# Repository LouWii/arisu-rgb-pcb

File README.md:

# Arisu Keyboard PCB - RGB & DIY mod

Arisu RGB Keyboard PCB, originally designed by [FateNozomi](https://github.com/FateNozomi), modified by [LouWii](https://github.com/LouWii).

The main differences with the original design are:

* RGB LEDs added for underglow (12 LEDs)
* Some components replaced with their through-hole version for easy soldering
* Micro-USB replaced with a mini-USB with through-hole soldering (for better strength)

The layout remains **unchanged** from the original design.

Original presentation:

> アリス PCB designed using KiCad. The layout is inspired by Lyn's EM7 and TGR Alice with some modification of my own.
>
> Key differences:
>
> * I removed the extra [B] key on the right half and shifted the [NM,.?] row to the left by 0.25U.
> * Shifted the 3 keys to the right and added arrow keys.
> * Tweaked the bottom so that the 1.5U keys doesn't protrude out a little.

> Shifting the [NM,.?] row to the left by 0.25U required quite some work on the arrangement of keys for the right half.
> As a result, this does not give the same typing experience as Lyn's EM7 and TGR Alice.
> Lyn's EM7 and TGR Alice uses the home row as the center point to vertically align both halves while I used the number row instead.
> Due to the nature of staggered keyboards, aligning using the number row resulted in the home row not being aligned.

Disclaimer: Use these files at your own risk.

## Gerber Files
Download the gerber files under [releases](https://github.com/FateNozomi/arisu-pcb/releases).

## Assembly
For the components required, you may refer to the bill of materials included along with the release as reference or load up the design file in KiCad.
All the components can be soldered using a regular soldering iron, though soldering the Micro USB receptacle might be the biggest hurdle.

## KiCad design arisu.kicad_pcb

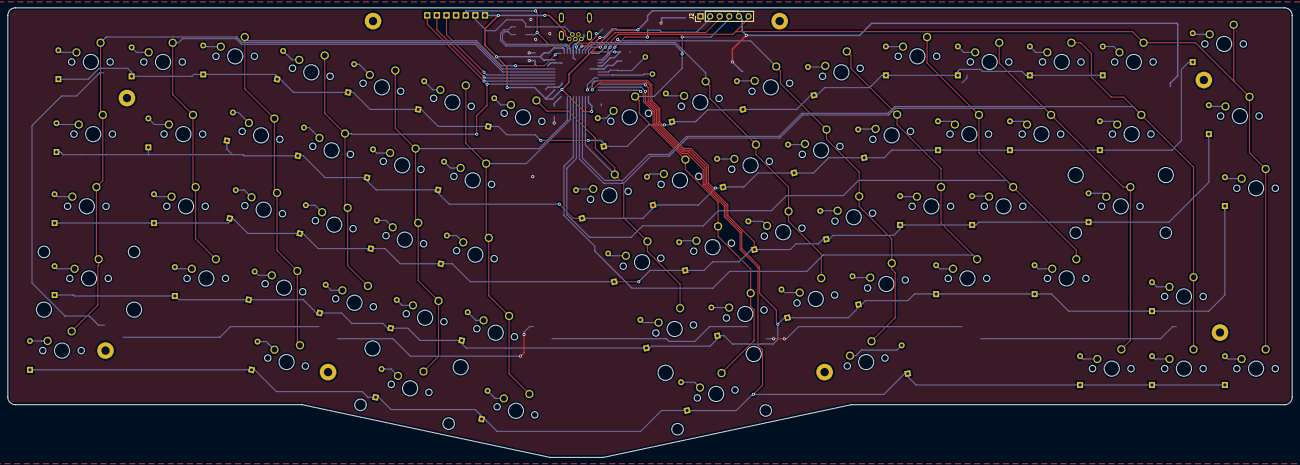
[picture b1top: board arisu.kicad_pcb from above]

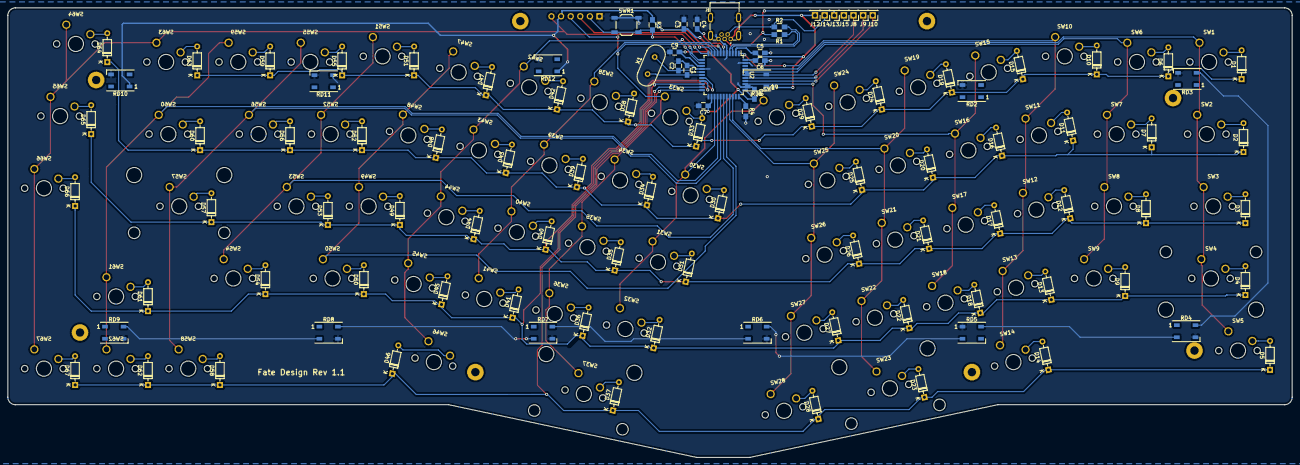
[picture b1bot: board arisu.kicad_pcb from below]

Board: 2 copper layers, 339.1 x 118.7 mm, 179 parts (103 on the bottom side), 114 nets.

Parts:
C1, C2: 22pF; C_0805_HandSoldering
C3: 10uF; C_0805_HandSoldering
C4: 1uF (±10%); C_0805_HandSoldering
C5: 1uF; C_0805_HandSoldering
C6, C7, C8, C9: 0.1uF; C_0805_HandSoldering
D1, D2, D3, D4, D5, D6, D7, D8, D9, D10, D11, D12, D13, D14, D15, D16, D17, D18, D19, D20, D21, D22, D23, D24, D25, D26, D27, D28, D29, D30, D31, D32, D33, D34, D35, D36, D37, D38, D39, D40, D41, D42, D43, D44, D45, D46, D47, D48, D49, D50, D51, D52, D53, D54, D55, D56, D57, D58, D59, D60, D61, D62, D63, D64, D65, D66, D67: D; D_DO-35_SOD27_P7.62mm_Horizontal
H1, H2, H3, H4, H5, H6, H7, H8: MountingHole; MountingHole_2.2mm_M2_Pad
J1: USB_B_Mini; Mini-USB-B_OMRON_XM7D-0512
J2: 1x6 2.54mm; PinHeader_1x06_P2.54mm_Vertical
J8: PF4; PinHeader_1x01_P2.54mm_Vertical
J9: PF5; PinHeader_1x01_P2.54mm_Vertical
J10: PF6; PinHeader_1x01_P2.54mm_Vertical
J12: VCC; PinHeader_1x01_P2.54mm_Vertical
J13: D+; PinHeader_1x01_P2.54mm_Vertical
J14: D-; PinHeader_1x01_P2.54mm_Vertical
J15: GND; PinHeader_1x01_P2.54mm_Vertical
R1, R2: 22; R_0805_HandSoldering
R3, R4: 10K; R_0805_HandSoldering
RD1, RD2, RD3, RD4, RD5, RD6, RD7, RD8, RD9, RD10, RD11, RD12: WS2812B; LED_WS2812B_PLCC4_5.0x5.0mm_P3.2mm
SW1, SW6, SW7, SW8, SW9, SW10, SW11, SW12, SW13, SW15, SW16, SW17, SW18, SW19, SW20, SW21, SW22, SW24, SW25, SW26, SW27, SW28, SW29, SW30, SW31, SW32, SW33, SW34, SW35, SW36, SW38, SW39, SW40, SW41, SW42, SW43, SW44, SW45, SW47, SW48, SW49, SW50, SW51, SW52, SW53, SW55, SW56, SW58, SW59, SW61, SW62, SW63, SW64, SW65, SW66, SW67: SW_Push; SW_Cherry_MX_1.00u_PCB
SW2, SW5, SW14, SW46, SW60: SW_Push; SW_Cherry_MX_1.50u_PCB
SW3, SW54: SW_Push; SW_Cherry_MX_1.75u_PCB
SW4: SW_Push; SW_Cherry_MX_2.25u_PCB
SW23: SW_Push; SW_Cherry_MX_2.00u_PCB_ReversedStabilizers
SW37: SW_Push; SW_Cherry_MX_2.75u_PCB_ReversedStabilizers
SW57: SW_Push; SW_Cherry_MX_2.25u_PCB_ReversedStabilizers
SWR1: SW_Push; SW_SPST_TL3342
U2: ATmega32U4-AU; TQFP-44_10x10mm_P0.8mm
X1: 16Mhz; Crystal_HC49-U_Vertical

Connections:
/MISO: J2.6, SW63.1, SW64.1, SW65.1, SW66.1, SW67.1, U2.11
/MOSI: J2.3, U2.10
/PF4: J8.1, U2.39
/PF5: J9.1, U2.38
/PF6: J10.1, U2.37
/SCK: J2.4, SW33.1, SW34.1, SW35.1, SW36.1, SW37.1, U2.9
/col0: SW1.1, SW2.1, SW3.1, SW4.1, SW5.1, U2.41
/col1: SW6.1, SW7.1, SW8.1, SW9.1, U2.40
/col2: SW10.1, SW11.1, SW12.1, SW13.1, SW14.1, U2.1
/col3: SW15.1, SW16.1, SW17.1, SW18.1, U2.36
/col4: SW19.1, SW20.1, SW21.1, SW22.1, SW23.1, U2.31
/col5: SW24.1, SW25.1, SW26.1, SW27.1, SW28.1, U2.30
/col6: SW29.1, SW30.1, SW31.1, SW32.1, U2.25
/col8: SW38.1, SW39.1, SW40.1, SW41.1, U2.8
/col9: SW42.1, SW43.1, SW44.1, SW45.1, SW46.1, U2.12
/col10: SW47.1, SW48.1, SW49.1, SW50.1, U2.29
/col11: SW51.1, SW52.1, SW53.1, SW54.1, U2.28
/col12: SW55.1, SW56.1, SW57.1, SW58.1, U2.27
/col13: SW59.1, SW60.1, SW61.1, SW62.1, U2.26
/row0: D1.1, D6.1, D10.1, D15.1, D19.1, D24.1, D29.1, D33.1, D38.1, D42.1, D47.1, D51.1, D55.1, D59.1, D63.1, U2.18
/row1: D2.1, D7.1, D11.1, D16.1, D20.1, D25.1, D30.1, D34.1, D39.1, D43.1, D48.1, D52.1, D56.1, D60.1, D64.1, U2.19
/row2: D3.1, D8.1, D12.1, D17.1, D21.1, D26.1, D31.1, D35.1, D40.1, D44.1, D49.1, D53.1, D57.1, D65.1, U2.20
/row3: D4.1, D9.1, D13.1, D18.1, D22.1, D27.1, D32.1, D36.1, D41.1, D45.1, D50.1, D54.1, D61.1, D66.1, U2.21
/row4: D5.1, D14.1, D23.1, D28.1, D37.1, D46.1, D58.1, D62.1, D67.1, U2.22
/~RES~: J2.2, R3.2, SWR1.2, U2.13
D+: R1.1, U2.4
D-: R2.1, U2.3
GND: C1.1, C2.2, C3.2, C4.2, C5.2, C6.2, C7.2, C8.2, C9.2, J1.5, J1.6, J2.1, J15.1, R4.2, RD1.3, RD2.3, RD3.3, RD4.3, RD5.3, RD6.3, RD7.3, RD8.3, RD9.3, RD10.3, RD11.3, RD12.3, SWR1.1, U2.5, U2.15, U2.23, U2.35, U2.43
unnamed: C4.1, U2.6
unnamed: D1.2, SW1.2
unnamed: D2.2, SW2.2
unnamed: D3.2, SW3.2
unnamed: D4.2, SW4.2
unnamed: D5.2, SW5.2
unnamed: D6.2, SW6.2
unnamed: D7.2, SW7.2
unnamed: D8.2, SW8.2
unnamed: D9.2, SW9.2
unnamed: D10.2, SW10.2
unnamed: D11.2, SW11.2
unnamed: D12.2, SW12.2
unnamed: D13.2, SW13.2
unnamed: D14.2, SW14.2
unnamed: D15.2, SW15.2
unnamed: D16.2, SW16.2
unnamed: D17.2, SW17.2
unnamed: D18.2, SW18.2
unnamed: D19.2, SW19.2
unnamed: D20.2, SW20.2
unnamed: D21.2, SW21.2
unnamed: D22.2, SW22.2
unnamed: D23.2, SW23.2
unnamed: D24.2, SW24.2
unnamed: D25.2, SW25.2
unnamed: D26.2, SW26.2
unnamed: D27.2, SW27.2
unnamed: D28.2, SW28.2
unnamed: D29.2, SW29.2
unnamed: D30.2, SW30.2
unnamed: D31.2, SW31.2
unnamed: D32.2, SW32.2
unnamed: D33.2, SW33.2
unnamed: D34.2, SW34.2
unnamed: D35.2, SW35.2
unnamed: D36.2, SW36.2
unnamed: D37.2, SW37.2
unnamed: D38.2, SW38.2
unnamed: D39.2, SW39.2
unnamed: D40.2, SW40.2
unnamed: D41.2, SW41.2
unnamed: D42.2, SW42.2
unnamed: D43.2, SW43.2
unnamed: D44.2, SW44.2
unnamed: D45.2, SW45.2
unnamed: D46.2, SW46.2
unnamed: D47.2, SW47.2
unnamed: D48.2, SW48.2
unnamed: D49.2, SW49.2
unnamed: D50.2, SW50.2
unnamed: D51.2, SW51.2
unnamed: D52.2, SW52.2
unnamed: D53.2, SW53.2
unnamed: D54.2, SW54.2
unnamed: D55.2, SW55.2
unnamed: D56.2, SW56.2
unnamed: D57.2, SW57.2
unnamed: D58.2, SW58.2
unnamed: D59.2, SW59.2
unnamed: D60.2, SW60.2
unnamed: D61.2, SW61.2
unnamed: D62.2, SW62.2
unnamed: D63.2, SW63.2
unnamed: D64.2, SW64.2
unnamed: D65.2, SW65.2
unnamed: D66.2, SW66.2
unnamed: D67.2, SW67.2
unnamed: J1.2, J14.1, R2.2
unnamed: J1.3, J13.1, R1.2
unnamed: R4.1, U2.33
unnamed: RD1.2, RD2.4
unnamed: RD2.2, RD3.4
unnamed: RD3.2, RD4.4
unnamed: RD4.2, RD5.4
unnamed: RD5.2, RD6.4
unnamed: RD6.2, RD7.4
unnamed: RD7.2, RD8.4
unnamed: RD8.2, RD9.4
unnamed: RD10.2, RD11.4
unnamed: RD9.2, RD10.4
unnamed: RD11.2, RD12.4
RGBIN: RD1.4, U2.32
VCC: C3.1, C5.1, C6.1, C7.1, C8.1, C9.1, J1.1, J2.5, J12.1, R3.1, RD1.1, RD2.1, RD3.1, RD4.1, RD5.1, RD6.1, RD7.1, RD8.1, RD9.1, RD10.1, RD11.1, RD12.1, U2.2, U2.7, U2.14, U2.24, U2.34, U2.44
XTAL1: C1.2, U2.17, X1.1
XTAL2: C2.1, U2.16, X1.2

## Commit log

2020-01-13 Replace components, place RGB leds, update traces - WIP
2020-01-13 add WIP BOM list, add 3d model for USB port
